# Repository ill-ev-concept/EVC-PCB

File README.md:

# EVC-PCB

*By: Himesh Nasaka*

Welcome to EV Concept's PCB Repo!

This is where all of our projects are stored. 

* Boards: Contains design files of all current boards being worked on
* Libs: Contains a wide selection of schematics, footprints, and models of components that are being used

# Getting Started

Start by having Git and KiCAD 10 downloaded. If you are using a older version of KiCAD, we recommend updating to the newest version. We also recommend installing Github Desktop in order to make the usage a bit cleaner.

Clone this repo. This can be either done through terminal or Github Desktop. Click the green dropdown labeled "<> Code" and select your preference of how to clone the repo. If using terminal, run the command below

```git clone [INSERT]```

If using Desktop, you can click the dropdown menu next to current repository, then "add", and finally "clone" where we can input the repo's url. 

# Setting Paths

After cloning, open KiCAD and find the "Preferences" dropdown and select "Configure Paths".
We are going to be adding three new paths. Create three new variables, ```EVC_SYMBOL_DIR```, ```EVC_FOOTPRINT_DIR```, and ```EVC_3DMODEL_DIR```. Link these to the location of the ```symbols```, ```footprints```, and ```3d_models``` folders contained with ```libs``` folder.

When designing, we will need KiCAD to know to look at a given library. We can do this by going to "Preferences" and finding either "Manage Symbol Libraries" or "Manage Footprint Libraries". Opening either brings up a window where we can select "Project Specific Libraries" where we can add paths. Click the folder icon and add the wanted library. If you set the path up correctly, the library path will contain  ```${EVC_SYMBOL_DIR}```, ```${EVC_FOOTPRINT_DIR}```, or ```${EVC_3DMODEL_DIR}```. 

# Contributing 

In order to begin designing, create a branch for your given board. This can be done through either the "current branch" dropdown in Desktop or using the command ```git checkout -b [branch name]```. You can swap branches using the same dropdown or either ```git checkout [branch name]```. 

This will be the branch where you will be doing your design work. Create a new KiCAD project and save the location into the boards folder of this repo. Everything onward will be traditional git. Use ```git add``` or check off the needed boxes on Desktop to add files for commit. ```git commit -m "[MESSAGE HERE]"``` will commit your changes. Make sure to write a meaningful commit message in order for good documentation. An example is shown below.

```git commit -m "Finished designing LDO and CANBus connectors, need to add MCU pinout and decoupling caps"```

Input both your contributions and the next required steps in order to give reminders to both yourself and your teammates. 

Once a board is finished or you want it reviewed, it must be submitted via a pull request. This can be done using ```git push -u origin [branch name]``` or by clicking the branch dropdown in Desktop and selecting the "create pull request" option.

This will open up a Github tab on your browser where you can edit your pull request. Give it a good title and description so the design choices are clear and understandable. A title will also help the leads parse what you guys want done. 

You'll see the image above if you use a command line prompt and go to the repo.

After the PR is submitted, we will decide on whether the board can be pushed to main or not. If it is not pushed, we will submit comments on what needs to be reviewed and edited. You can view open PRs and their comments in Github.

Apart from designing in KiCAD, it is important to be updating the libs folder when any new schematic, footprint, or model is added. First make sure the IC you want to add isn't currently within our library. Add the path to the specific library which is detailed more above. If the IC is not located in it's library, open Symbol/Footprint editor and select the library you want to add to. I recommended clicking the "View" dropdown, selecting the "Panels" option and adding the "Library Tree" option in order to easily see the connected libraries. 

From this, import the downloaded model and save the file. From there, push the updated library files and create a pull request. The leads will then check your work and merge it into main so everyone can use the IC.

When making pull requests for ICs, make sure to push them individually rather than with changes to other files. This will make it more clear for reviewers to understand that library files are being edited in addition to making sure that the change will be pushed to main. If you push with changes to your board and the pull request is not granted, people will not have access to the IC you have imported. 

Because the libs folder will be constantly updated, its also important to keep your branch up to date with new changes. We can layer on changes from main into our branch using a few different methods but the main one we will be using is merge. Run the command ```git fetch origin``` and then ```git merge origin``` in order to update changes. In Desktop, you can select "Update from main" from the "Branch" dropdown. 

This should not change any local files that is stored and will update the libs folder to have the newest selection of ICs. I recommend doing this every time you work on your boards. It will also make sure a merge conflict won't be created, in which the same file from two different pull requests is edited, causing a lot of hassle for the writers of this repo. 

A general outline of what the workflow may look like is shown below:

```git checkout [branch name]``` -> Run this to swap to the branch you want to work on

```git fetch origin``` -> Run this to pull updates from main. Important for having updated libs

```git merge origin/main``` -> Merges the changes from the above command

```git add [file name]``` -> Add files for commit. When updating library files, make sure to add them in individual PRs

```git commit -m "[message here]"``` -> Commits your changes to be pushed into your branch

```git push -u origin [branch name]``` -> Run this command the first time you make the branch. It will link your branch to Github. 

```git push``` -> Pushes your changes. After, you can go to Github and create a pull request for the changes to be pushed into main. **Don't create a PR for every change you do.** Only create pull requests **IF** you are editing the libs folder **OR** you are submitting for board revision **OR** it is the final revision of the board.

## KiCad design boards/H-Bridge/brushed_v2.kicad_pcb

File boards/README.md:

# Boards!

This is the location where you will be pushing your KiCAD files to. 
Each file should be it's own project. You should only be pushing 5 different files
- kicad_pro
- kicad_sch
- kicad_pcb
- fp-lib-table
- sym-lib-table

*Nothing else should be pushed*

I'll be adding more details later on

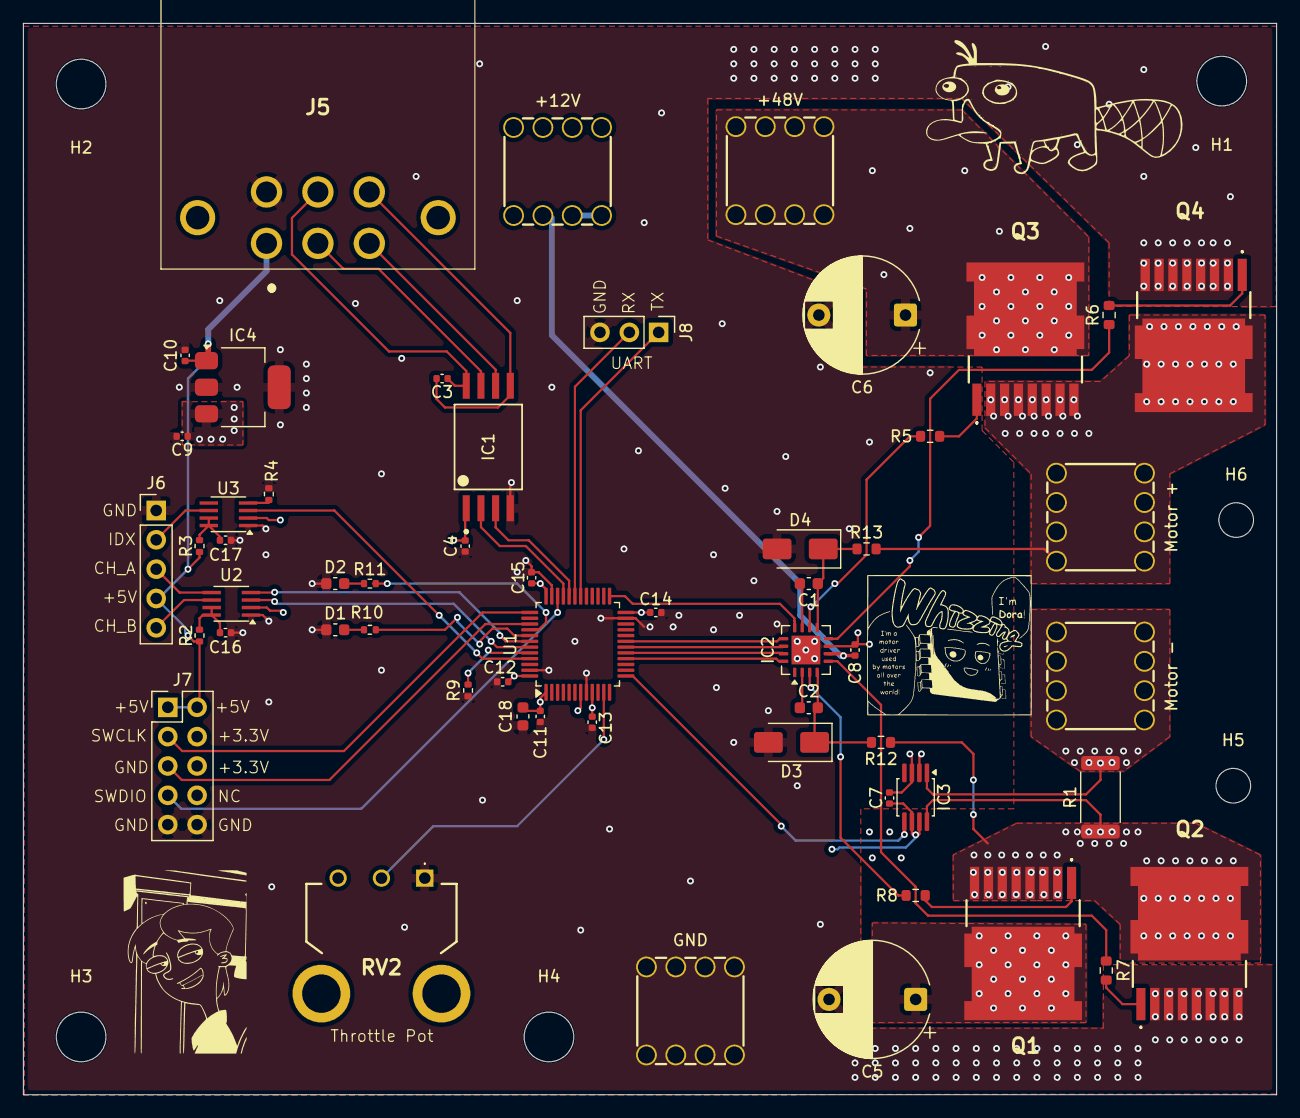
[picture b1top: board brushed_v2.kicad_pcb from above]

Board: 4 copper layers, 108.5 x 92.8 mm, 62 parts (0 on the bottom side), 52 nets.

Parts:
+12V: 12V+; WP-BUTR_7460307
+48V: V+; WP-BUTR_7460307
C1: 1uf; C_0603_1608Metric
C2: 1uF; C_0603_1608Metric
C3, C4, C7, C8, C11, C12, C13, C14, C15, C16, C17: 0.1uF; C_0402_1005Metric
C5, C6: 470uF; CP_Radial_D10.0mm_P7.50mm
C9, C10: 1uF; C_0402_1005Metric
C18: 4.7uF; C_0603_1608Metric
D1, D2: LED; C_0603_1608Metric
D3, D4: SS1200; D_SMA
GND: V-; WP-BUTR_7460307
H1, H2, H3, H4: MountingHole; MountingHole_4.3mm_M4
H5, H6: MountingHole; MountingHole_3mm
IC1: ISO1042QDWVQ1; DWV0008A-IPC_A
IC2: MIC4606-1YML-TR; QFN-16-1EP_4x4mm_P0.65mm_EP2.5x2.5mm
IC3: AD8410AWBRZ-RL; MSOP-8_3x3mm_P0.65mm
IC4: TC1108-3.3VDBTR; SOT-223
J5: DTF13-6P; DTF136P
J6: Encoder; PinHeader_1x05_P2.54mm_Vertical
J7: Prog_Header; PinHeader_2x05_P2.54mm_Vertical
J8: UART; PinHeader_1x03_P2.54mm_Vertical
Motor +: Motor-; WP-BUTR_7460307
Motor -: Motor+; WP-BUTR_7460307
Q1, Q2, Q3, Q4: NTBLS4D0N15MC
R1: .001; R_2512_6332Metric
R2, R3: 200k; R_0402_1005Metric
R4, R9: 10k; R_0402_1005Metric
R5, R6, R7, R8: 10; R_0603_1608Metric
R10, R11: 330; R_0402_1005Metric
R12, R13: 3; R_0603_1608Metric
RV2: Debug Throttle; P120PKY25BR10K
U1: STM32F103C8Tx; LQFP-48_7x7mm_P0.5mm
U2, U3: LSF0102DCUR; SSOP-8_2.95x2.8mm_P0.65mm

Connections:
+3.3V: C4.1, C7.1, C9.1, C11.1, C12.1, C13.1, C14.1, C15.1, C18.1, IC1.1 (VCC1), IC3.6 (VS), IC3.7 (VREF1), IC4.3 (VOUT), J7.4, J7.6, RV2.3, U1.1 (VBAT), U1.7 (NRST), U1.9 (VDDA), U1.24 (VDD), U1.36 (VDD), U1.48 (VDD), U2.2 (VREF_A), U3.2 (VREF_A)
+5V: C10.1, IC4.1 (VIN), J5.1, J6.4, J7.1, J7.2, R2.1, R3.1
+12V: +12V.1 (Pin_1_1), C8.1, IC2.6 (VDD)
+48V: +48V.1 (Pin_1_1), C5.1, C6.1, Q1.9 (D_1), Q1.10 (D_2), Q1.11 (D_3), Q1.12 (D_4), Q1.13 (D_5), Q3.9 (D_1), Q3.10 (D_2), Q3.11 (D_3), Q3.12 (D_4), Q3.13 (D_5)
/High Voltage&Sense/AHS: C2.2, D3.1 (K), IC2.4 (AHS), R12.2
/High Voltage&Sense/BHS: C1.1, D4.1 (K), IC2.9 (BHS), R13.1
/High Voltage&Sense/GATEA_HIGH: Q1.8 (G), R8.2
/High Voltage&Sense/GATEA_LOW: Q2.8 (G), R7.1
/High Voltage&Sense/GATEB_HIGH: Q3.8 (G), R5.2
/High Voltage&Sense/GATEB_LOW: Q4.8 (G), R6.2
/High Voltage&Sense/SHUNT+: IC3.8 (+IN), Q1.1 (S_1), Q1.2 (S_2), Q1.3 (S_3), Q1.4 (S_4), Q1.5 (S_5), Q1.6 (S_6), Q1.7 (S_7), Q2.9 (D_1), Q2.10 (D_2), Q2.11 (D_3), Q2.12 (D_4), Q2.13 (D_5), R1.1, R12.1
/High Voltage&Sense/SHUNT-: IC3.1 (-IN), Motor -.1 (Pin_1_1), R1.2
/MCU&Low_Voltage/AHI: IC2.16 (AHI), U1.16 (PA6)
/MCU&Low_Voltage/ALI: IC2.15 (ALI), U1.17 (PA7)
/MCU&Low_Voltage/BHI: IC2.13 (BHI), U1.19 (PB1)
/MCU&Low_Voltage/BLI: IC2.14 (BLI), U1.18 (PB0)
/MCU&Low_Voltage/CAN5V: C3.1, IC1.8 (VCC2), J5.5
/MCU&Low_Voltage/CANGND: C3.2, IC1.5 (GND2), J5.4
/MCU&Low_Voltage/CANH: IC1.7 (CANH), J5.2
/MCU&Low_Voltage/CANL: IC1.6 (CANL), J5.3
/MCU&Low_Voltage/CAN_RX: IC1.3 (RXD), U1.32 (PA11)
/MCU&Low_Voltage/CAN_TX: IC1.2 (TXD), U1.33 (PA12)
/MCU&Low_Voltage/CHA_3.3: U1.42 (PB6), U2.4 (A2)
/MCU&Low_Voltage/CHB_3.3: U1.43 (PB7), U2.3 (A1)
/MCU&Low_Voltage/CH_A: J6.3, U2.5 (B2)
/MCU&Low_Voltage/CH_B: J6.5, U2.6 (B1)
/MCU&Low_Voltage/GATE_EN: IC2.12 (EN), U1.25 (PB12)
/MCU&Low_Voltage/IDX: J6.2, U3.6 (B1)
/MCU&Low_Voltage/IDX_3.3: U1.45 (PB8), U3.3 (A1)
/MCU&Low_Voltage/LED_1: R10.1, U1.41 (PB5)
/MCU&Low_Voltage/LED_2: R11.1, U1.40 (PB4)
/MCU&Low_Voltage/POT_IN: RV2.2, U1.11 (PA1)
/MCU&Low_Voltage/SENSE: IC3.5 (OUT), U1.13 (PA3)
/MCU&Low_Voltage/SWCLK: J7.3, U1.37 (PA14)
/MCU&Low_Voltage/SWDIO: J7.7, U1.34 (PA13)
/MCU&Low_Voltage/SWO: J7.5, U1.39 (PB3)
/MCU&Low_Voltage/UART_RX: J8.2, U1.31 (PA10)
/MCU&Low_Voltage/UART_TX: J8.1, U1.30 (PA9)
GND: C4.2, C5.2, C6.2, C7.2, C8.2, C9.2, C10.2, C11.2, C12.2, C13.2, C14.2, C15.2, C16.2, C17.2, C18.2, D1.1 (K), D2.1 (K), D3.2 (A), D4.2 (A), GND.1 (Pin_1_1), IC1.4 (GND1), IC2.7 (VSS), IC2.17 (GND), IC3.2 (GND), IC3.3 (VREF2), IC4.2 (GND_1), IC4.4 (GND_2), J5.6, J6.1, J7.9, J7.10, J8.3, Q2.1 (S_1), Q2.2 (S_2), Q2.3 (S_3), Q2.4 (S_4), Q2.5 (S_5), Q2.6 (S_6), Q2.7 (S_7), Q4.1 (S_1), Q4.2 (S_2), Q4.3 (S_3), Q4.4 (S_4), Q4.5 (S_5), Q4.6 (S_6), Q4.7 (S_7), R4.1, R9.2, RV2.1, U1.8 (VSSA), U1.23 (VSS), U1.35 (VSS), U1.47 (VSS), U2.1 (GND), U3.1 (GND)
unnamed: D1.2 (A), R10.2
unnamed: D2.2 (A), R11.2
unnamed: C2.1, IC2.2 (AHB)
unnamed: IC2.3 (AHO), R8.1
unnamed: IC2.5 (ALO), R7.2
unnamed: C1.2, IC2.11 (BHB)
unnamed: IC2.10 (BHO), R5.1
unnamed: IC2.8 (BLO), R6.1
unnamed: Motor +.1 (Pin_1_1), Q3.1 (S_1), Q3.2 (S_2), Q3.3 (S_3), Q3.4 (S_4), Q3.5 (S_5), Q3.6 (S_6), Q3.7 (S_7), Q4.9 (D_1), Q4.10 (D_2), Q4.11 (D_3), Q4.12 (D_4), Q4.13 (D_5), R13.2
unnamed: R9.1, U1.44 (BOOT0)
unnamed: C16.1, R2.2, U2.7 (VREF_B), U2.8 (EN)
unnamed: R4.2, U3.4 (A2)
unnamed: C17.1, R3.2, U3.7 (VREF_B), U3.8 (EN)

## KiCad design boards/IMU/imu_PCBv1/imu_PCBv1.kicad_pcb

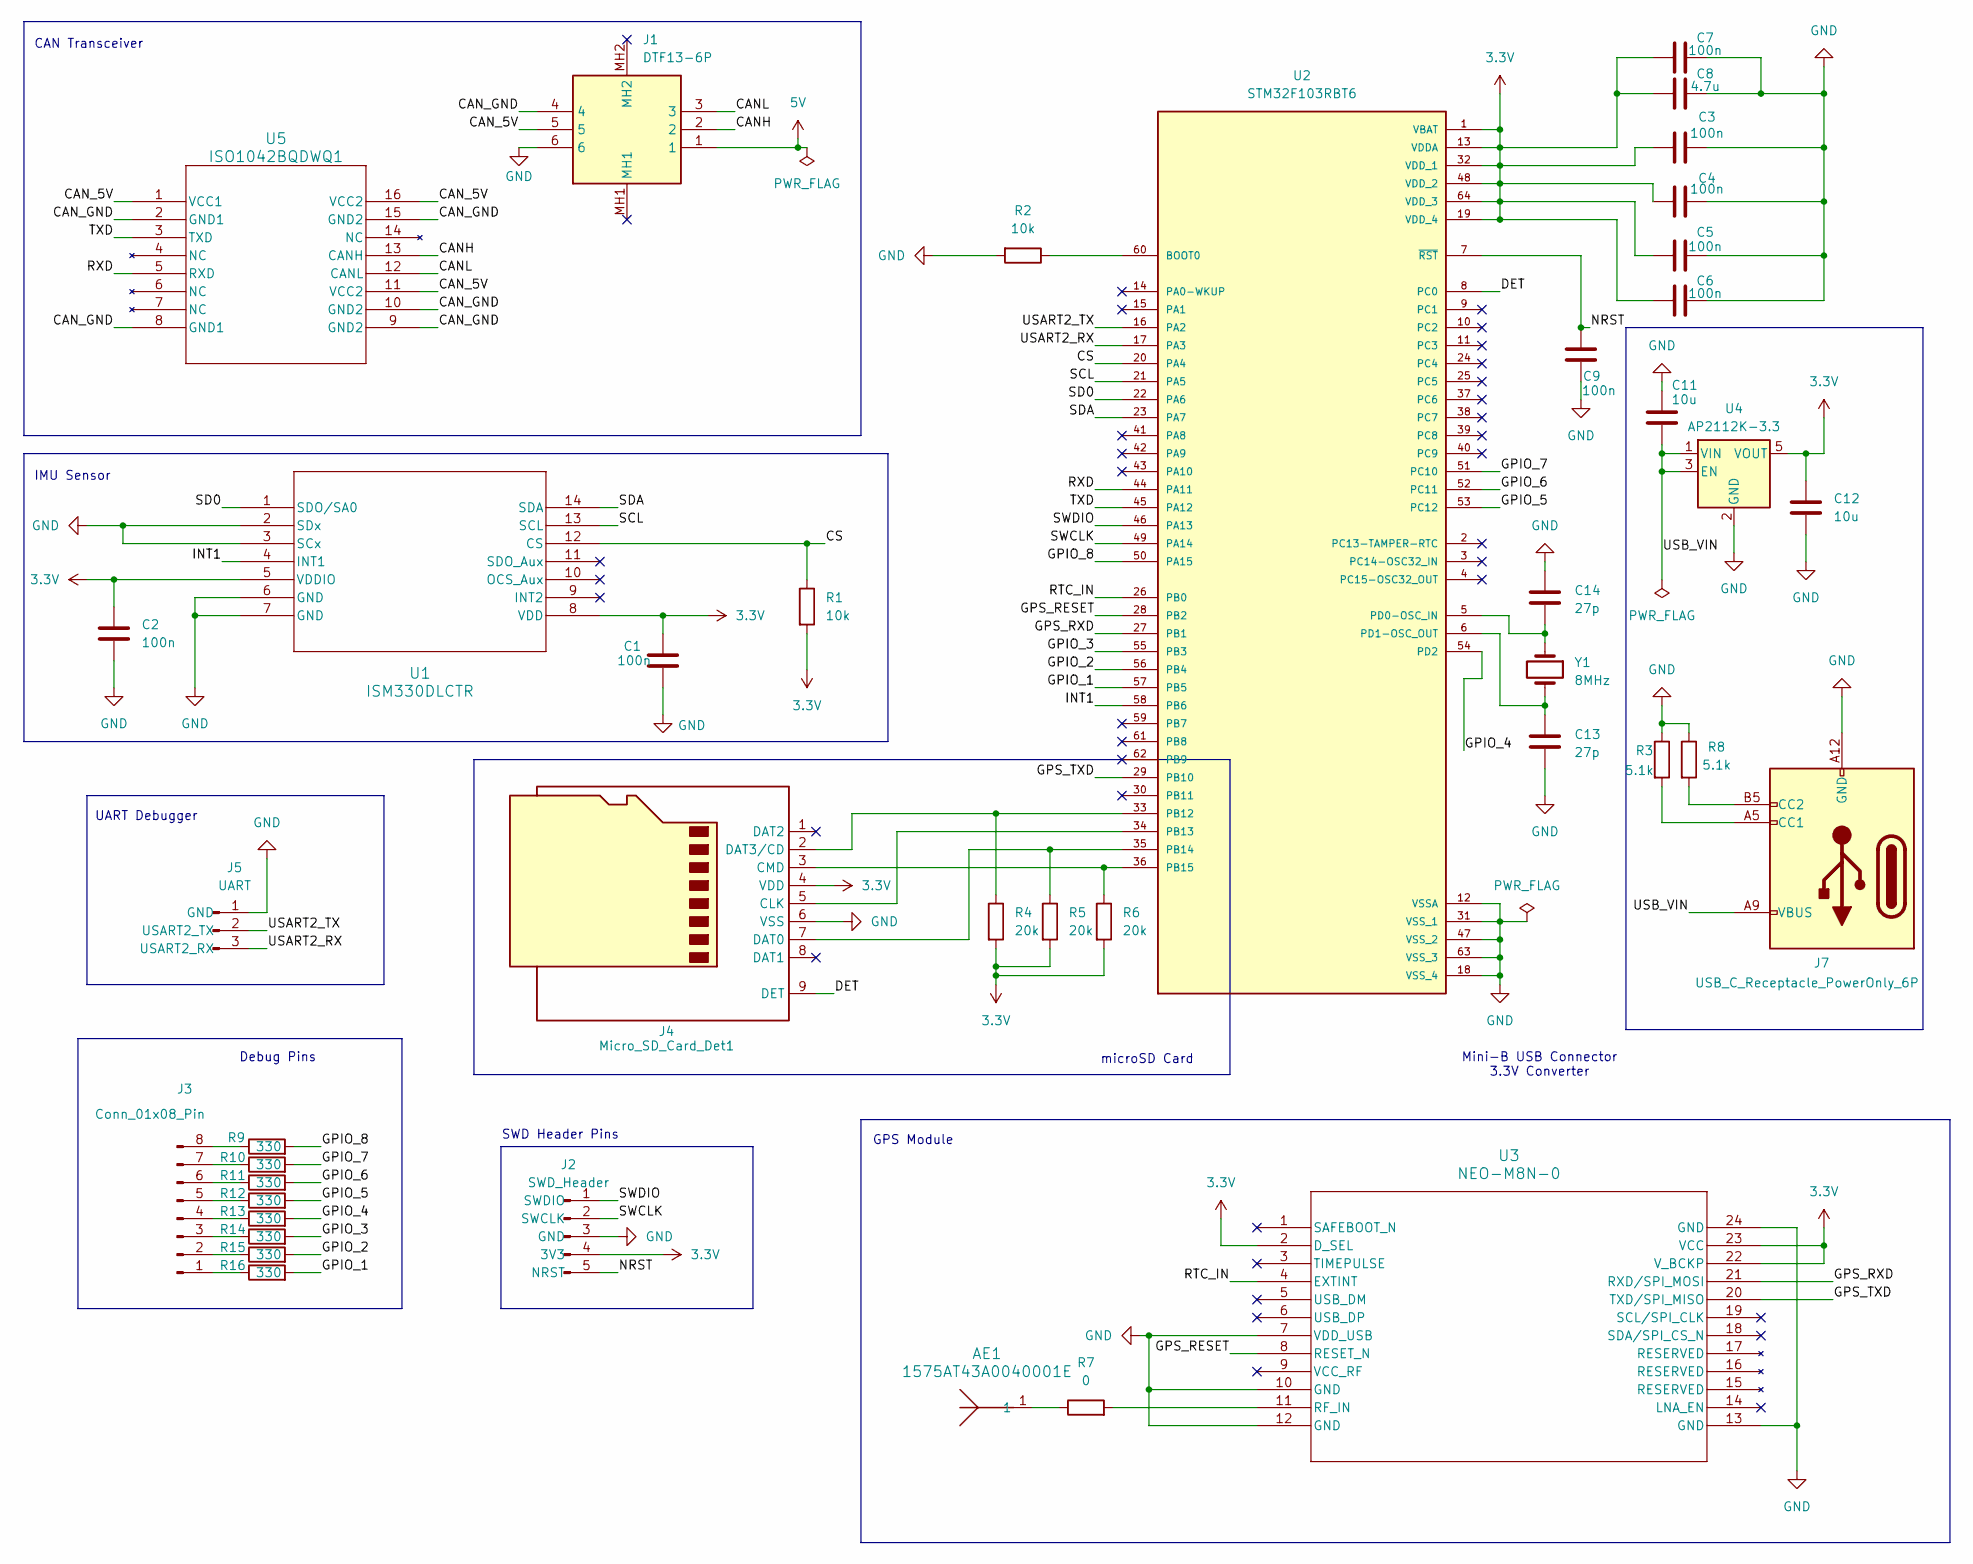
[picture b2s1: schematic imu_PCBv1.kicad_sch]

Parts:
AE1: 1575AT43A0040001E; antenna
C1, C2, C3, C4, C5, C6, C7, C9: 100n; C_0603_1608Metric_Pad1.08x0.95mm_HandSolder
C8: 4.7u; C_0603_1608Metric_Pad1.08x0.95mm_HandSolder
C11, C12: 10u; C_0603_1608Metric_Pad1.08x0.95mm_HandSolder
C13, C14: 27p; C_0603_1608Metric_Pad1.08x0.95mm_HandSolder
J1: DTF13-6P; EVC_CANconnector; Manufacturer_Part_Number DTF13-6P; Mouser Part Number 571-DTF13-6P
J2: SWD_Header; PinHeader_1x05_P2.54mm_Vertical
J3: Conn_01x08_Pin; PinHeader_1x08_P2.54mm_Vertical
J4: Micro_SD_Card_Det1; microSD_CardConnector_MSD-4-A
J5: UART; FanPinHeader_1x03_P2.54mm_Vertical
J7: USB_C_Receptacle_PowerOnly_6P; USB_Connector
R1, R2: 10k; R_0603_1608Metric_Pad0.98x0.95mm_HandSolder
R3, R8: 5.1k; R_0603_1608Metric_Pad0.98x0.95mm_HandSolder
R4, R5, R6: 20k; R_0603_1608Metric_Pad0.98x0.95mm_HandSolder
R7: 0; R_0603_1608Metric_Pad0.98x0.95mm_HandSolder
R9, R10, R11, R12, R13, R14, R15, R16: 330; R_0603_1608Metric_Pad0.98x0.95mm_HandSolder
U1: ISM330DLCTR; ISM330DLCTR-M
U2: STM32F103RBT6; STM32F103RBT6-10x10mm; PARTREV 20; DigiKey_Part_Number 497-6066-ND
U3: NEO-M8N-0; SNAP_NEO-M8N
U4: AP2112K-3.3; LinearRegulator_DIO-M
U5: ISO1042BQDWQ1; CAN-M
Y1: 8MHz; SOT-323_SC-70

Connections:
3.3V: C1.2, C2.2, C3.2, C4.2, C5.2, C6.2, C7.2, C8.2, C12.1, J2.4 (3V3), J4.4 (VDD), R1.2, R4.2, R5.2, R6.2, U1.5 (VDDIO), U1.8 (VDD), U2.1 (VBAT), U2.13 (VDDA), U2.19 (VDD_4), U2.32 (VDD_1), U2.48 (VDD_2), U2.64 (VDD_3), U3.2 (D_SEL), U3.22 (V_BCKP), U3.23 (VCC), U4.5 (VOUT)
5V: J1.1
/CANH: J1.2, U5.13 (CANH)
/CANL: J1.3, U5.12 (CANL)
/CAN_5V: J1.5, U5.1 (VCC1), U5.11 (VCC2), U5.16 (VCC2)
/CAN_GND: J1.4, U5.2 (GND1), U5.8 (GND1), U5.9 (GND2), U5.10 (GND2), U5.15 (GND2)
/CS: R1.1, U1.12 (CS), U2.20 (PA4)
/DET: J4.9 (DET), U2.8 (PC0)
/GPIO_1: R16.2, U2.57 (PB5)
/GPIO_2: R15.2, U2.56 (PB4)
/GPIO_3: R14.2, U2.55 (PB3)
/GPIO_4: R13.2, U2.54 (PD2)
/GPIO_5: R12.2, U2.53 (PC12)
/GPIO_6: R11.2, U2.52 (PC11)
/GPIO_7: R10.2, U2.51 (PC10)
/GPIO_8: R9.2, U2.50 (PA15)
/GPS_RESET: U2.28 (PB2), U3.8 (RESET_N)
/GPS_RXD: U2.27 (PB1), U3.21 (RXD/SPI_MOSI)
/GPS_TXD: U2.29 (PB10), U3.20 (TXD/SPI_MISO)
/INT1: U1.4 (INT1), U2.58 (PB6)
/NRST: C9.2, J2.5 (NRST), U2.7 (~RST)
/RTC_IN: U2.26 (PB0), U3.4 (EXTINT)
/RXD: U2.44 (PA11), U5.5 (RXD)
/SCL: U1.13 (SCL), U2.21 (PA5)
/SD0: U1.1 (SDO/SA0), U2.22 (PA6)
/SDA: U1.14 (SDA), U2.23 (PA7)
/SWCLK: J2.2 (SWCLK), U2.49 (PA14)
/SWDIO: J2.1 (SWDIO), U2.46 (PA13)
/TXD: U2.45 (PA12), U5.3 (TXD)
/USART2_RX: J5.3 (USART2_RX), U2.17 (PA3)
/USART2_TX: J5.2 (USART2_TX), U2.16 (PA2)
/USB_VIN: C11.2, J7.A9 (VBUS), J7.B9 (VBUS), U4.1 (VIN), U4.3 (EN)
GND: C1.1, C2.1, C3.1, C4.1, C5.1, C6.1, C7.1, C8.1, C9.1, C11.1, C12.2, C13.2, C14.1, J1.6, J2.3 (GND), J4.6 (VSS), J5.1 (GND), J7.A12 (GND), J7.B12 (GND), R2.2, R3.1, R8.1, U1.2 (SDx), U1.3 (SCx), U1.6 (GND), U1.7 (GND), U2.12 (VSSA), U2.18 (VSS_4), U2.31 (VSS_1), U2.47 (VSS_2), U2.63 (VSS_3), U3.7 (VDD_USB), U3.10 (GND), U3.12 (GND), U3.13 (GND), U3.24 (GND), U4.2 (GND)
unnamed: AE1.1 (1_1), R7.1
unnamed: J3.1, R16.1
unnamed: J3.2, R15.1
unnamed: J3.3, R14.1
unnamed: J3.4, R13.1
unnamed: J3.5, R12.1
unnamed: J3.6, R11.1
unnamed: J3.7, R10.1
unnamed: J3.8, R9.1
unnamed: J4.5 (CLK), U2.34 (PB13)
unnamed: J4.3 (CMD), R6.1, U2.36 (PB15)
unnamed: J4.7 (DAT0), R5.1, U2.35 (PB14)
unnamed: J4.2 (DAT3/CD), R4.1, U2.33 (PB12)
unnamed: J7.A5 (CC1), R3.2
unnamed: J7.B5 (CC2), R8.2
unnamed: R2.1, U2.60 (BOOT0)
unnamed: C14.2, U2.5 (PD0-OSC_IN), Y1.1
unnamed: C13.1, U2.6 (PD1-OSC_OUT), Y1.2
unnamed: R7.2, U3.11 (RF_IN)

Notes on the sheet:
microSD Card
GPS Module
Mini-B USB Connector 3.3V Converter
UART Debugger
Debug Pins
SWD Header Pins
IMU Sensor
CAN Transceiver

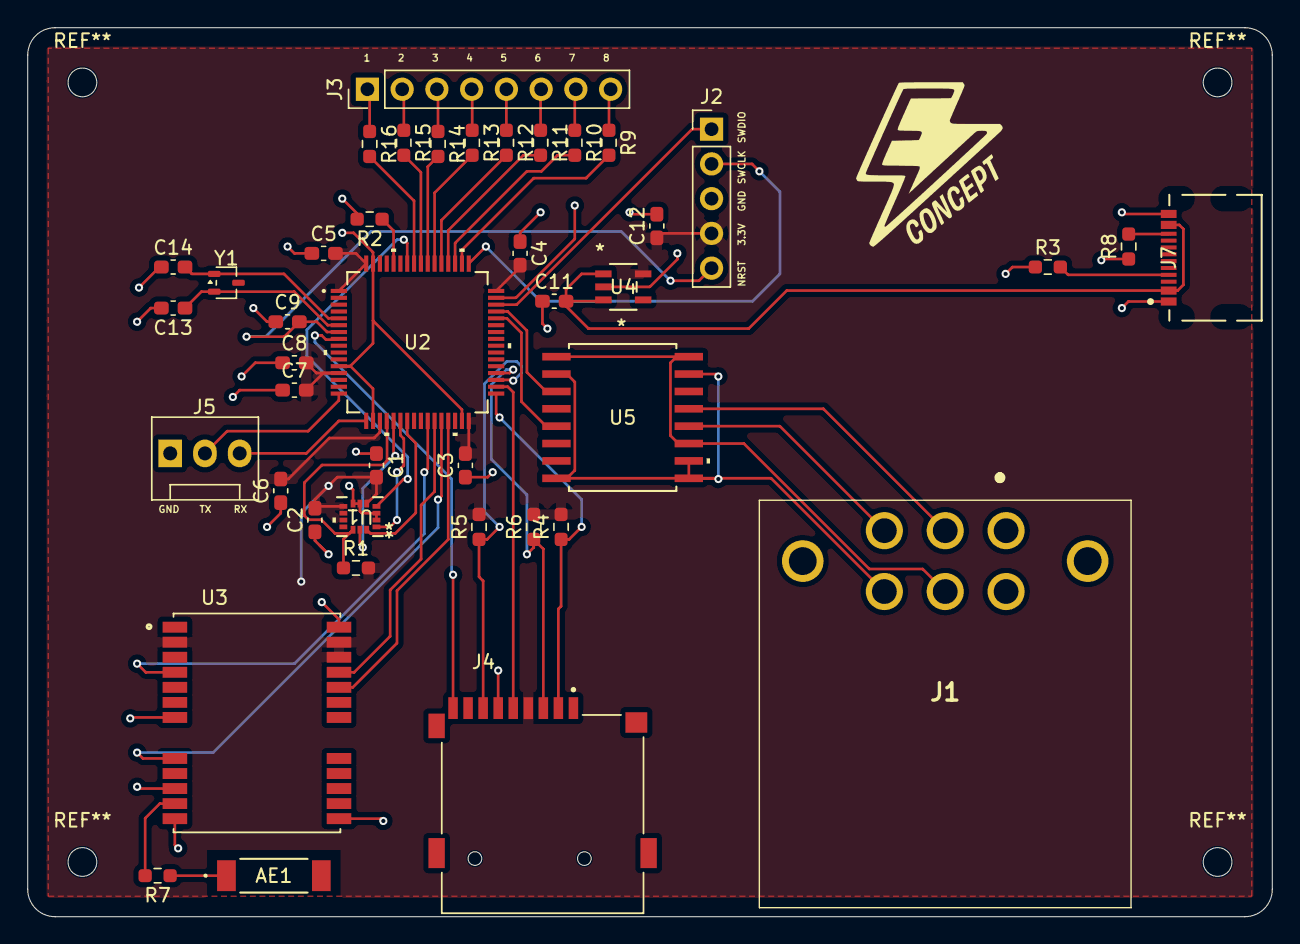
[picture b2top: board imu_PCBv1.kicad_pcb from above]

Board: 2 copper layers, 91.0 x 65.0 mm, 42 parts (0 on the bottom side), 51 nets.

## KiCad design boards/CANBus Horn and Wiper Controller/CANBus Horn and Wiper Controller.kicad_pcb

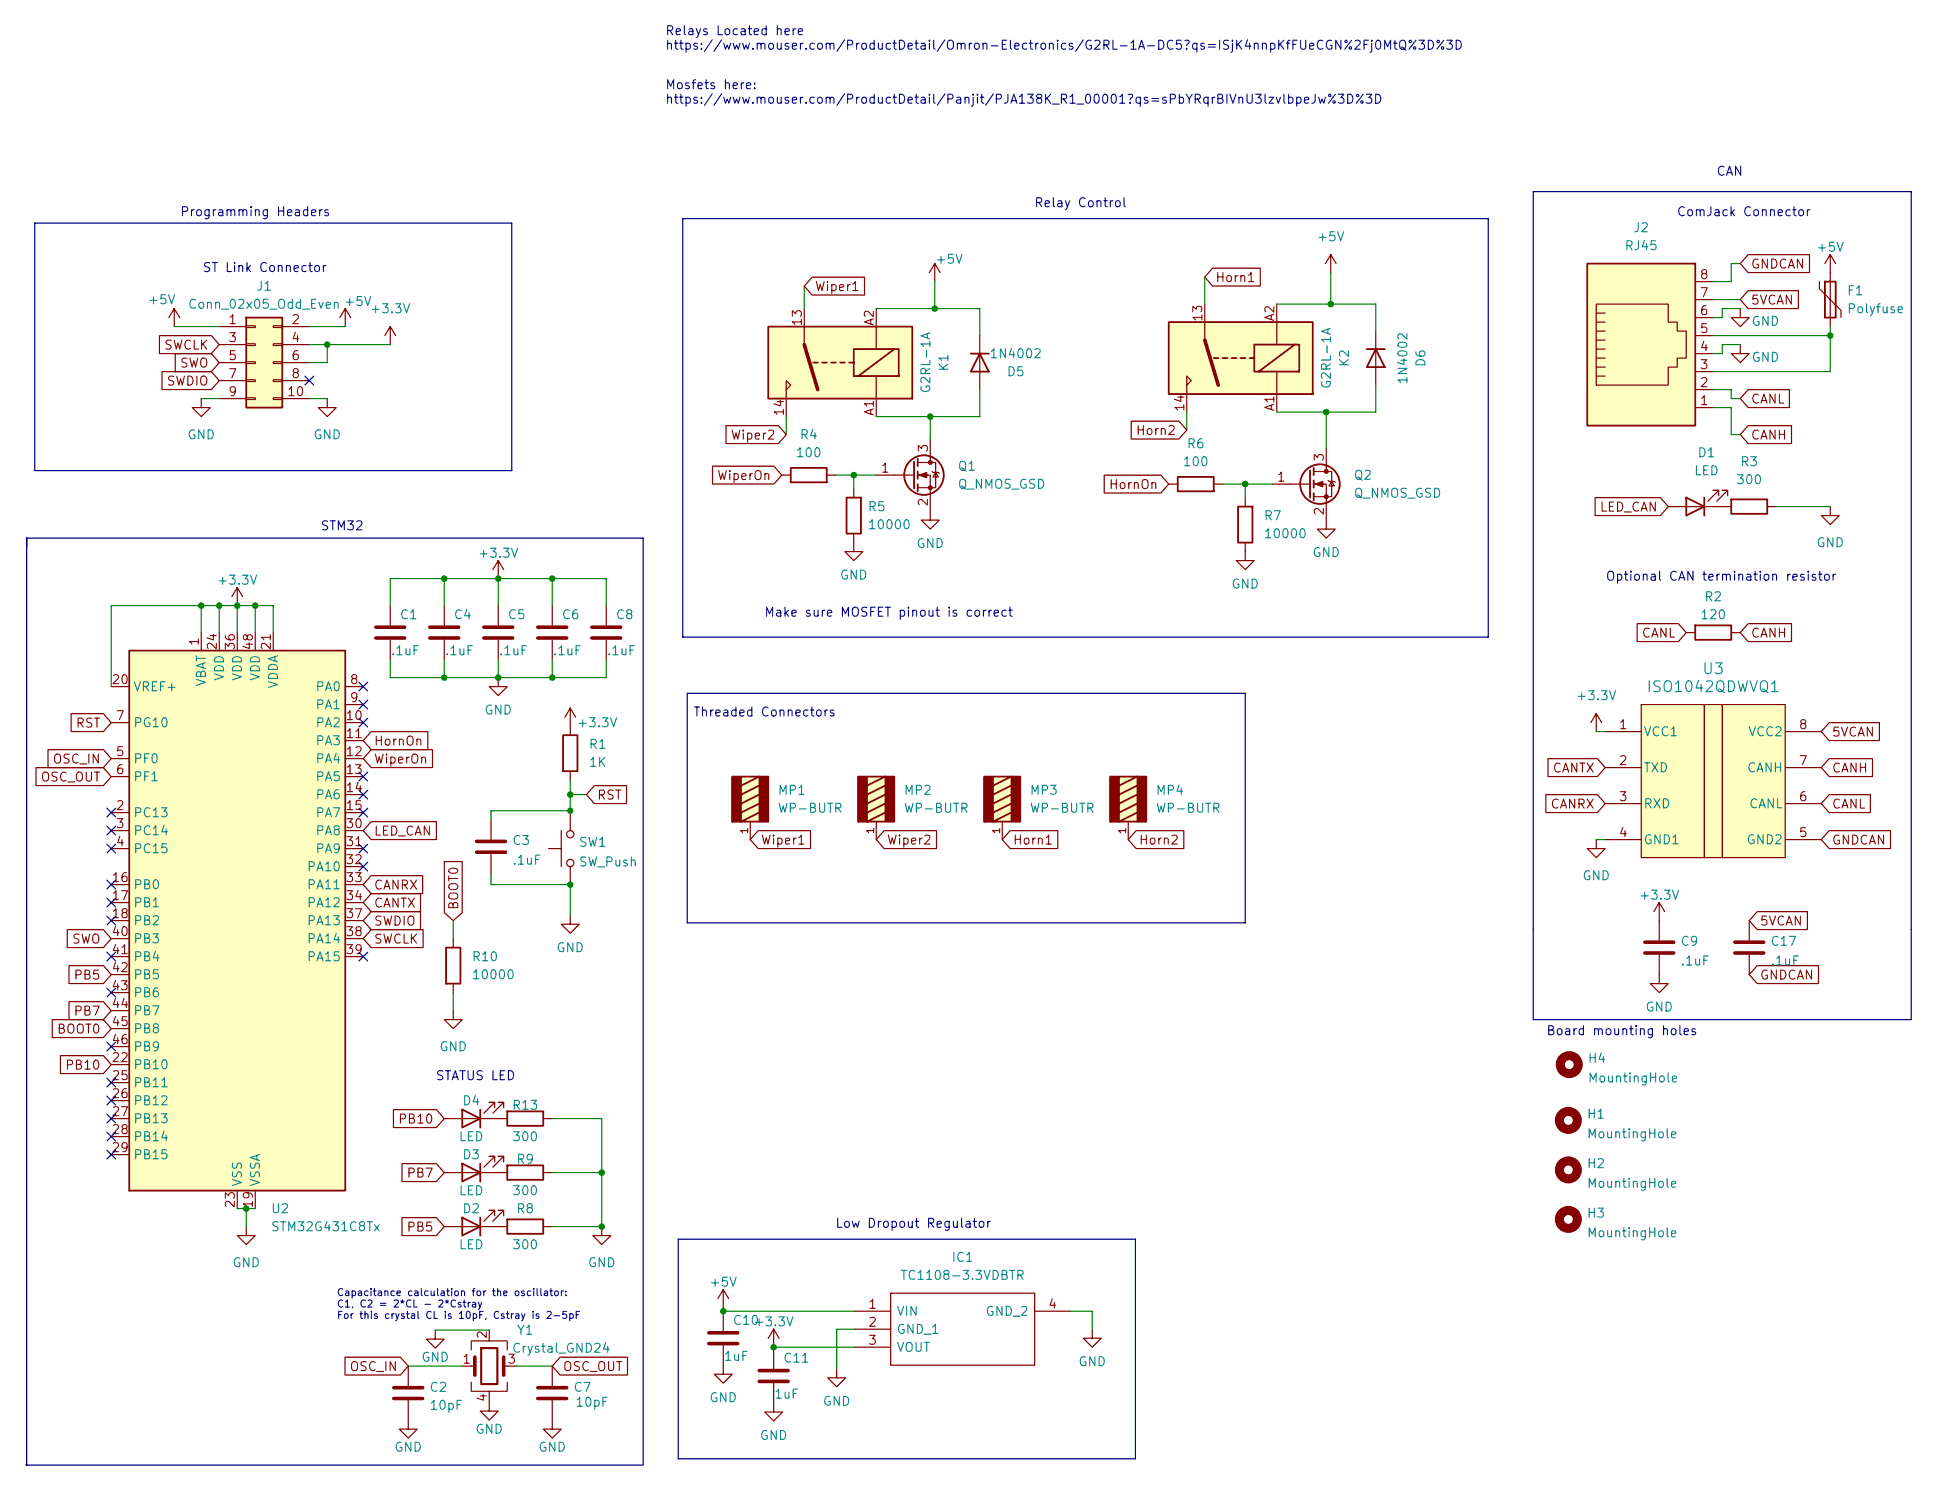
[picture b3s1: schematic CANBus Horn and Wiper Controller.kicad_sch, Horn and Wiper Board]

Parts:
C1, C3, C4, C5, C6, C8, C9, C17: .1uF; C_0805_2012Metric
C2, C7: 10pF; C_0603_1608Metric
C10, C11: 1uF; C_0805_2012Metric
D1, D2, D3, D4: LED; LED_0603_1608Metric
D5, D6: 1N4002; D_DO-41_SOD81_P10.16mm_Horizontal
F1: Polyfuse; Fuse_0805_2012Metric
H1, H2, H3, H4: MountingHole; MountingHole_3.2mm_M3
IC1: TC1108-3.3VDBTR; SOT230P700X180-4N; Mouser Part Number 579-TC1108-3.3VDBTR
J1: Conn_02x05_Odd_Even; PinSocket_2x05_P2.54mm_Vertical
J2: RJ45; RJ45_Amphenol_54602-x08_Horizontal
K1, K2: G2RL-1A; Relay_SPST_Omron_G2RL-1A
MP1, MP2, MP3, MP4: WP-BUTR; WP-BUTR_7460307; DigiKey_Part_Number 732-3201-ND
Q1, Q2: Q_NMOS_GSD; SOT-23-3
R1: 1K; R_0805_2012Metric
R2: 120; R_0805_2012Metric
R3, R8, R9, R13: 300; R_0805_2012Metric
R4, R6: 100; R_0805_2012Metric
R5, R7: 10000; R_0805_2012Metric
R10: 10000; R_0508_1220Metric
SW1: SW_Push; SW_Push_SPST_NO_Alps_SKRK
U2: STM32G431C8Tx; LQFP-48_7x7mm_P0.5mm
U3: ISO1042QDWVQ1; SOIC8_ISO1042-Q1
Y1: Crystal_GND24; Crystal_SMD_3225-4Pin_3.2x2.5mm

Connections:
5VCAN: C17.1, J2.7, U3.8 (VCC2)
+3.3V: C1.1, C4.1, C5.1, C6.1, C8.1, C9.1, C11.1, IC1.3 (VOUT), J1.4, J1.6, R1.1, U2.1 (VBAT), U2.20 (VREF+), U2.21 (VDDA), U2.24 (VDD), U2.36 (VDD), U2.48 (VDD), U3.1 (VCC1)
+5V: C10.1, D5.1 (K), D6.1 (K), F1.1, IC1.1 (VIN), J1.1, J1.2, K1.A2, K2.A2
BOOT0: R10.1, U2.45 (PB8)
CANH: J2.1, R2.1, U3.7 (CANH)
CANL: J2.2, R2.2, U3.6 (CANL)
CANRX: U2.33 (PA11), U3.3 (RXD)
CANTX: U2.34 (PA12), U3.2 (TXD)
GND: C1.2, C2.2, C3.2, C4.2, C5.2, C6.2, C7.2, C8.2, C9.2, C10.2, C11.2, IC1.2 (GND_1), IC1.4 (GND_2), J1.9, J1.10, J2.4, J2.6, Q1.2 (S), Q2.2 (S), R3.1, R5.1, R7.1, R8.1, R9.1, R10.2, R13.1, SW1.1, U2.19 (VSSA), U2.23 (VSS), U2.35 (VSS), U2.47 (VSS), U3.4 (GND1), Y1.2, Y1.4
GNDCAN: C17.2, J2.8, U3.5 (GND2)
Horn1: K2.13, MP3.1, MP3.2, MP3.3, MP3.4, MP3.5, MP3.6, MP3.7, MP3.8
Horn2: K2.14, MP4.1, MP4.2, MP4.3, MP4.4, MP4.5, MP4.6, MP4.7, MP4.8
HornOn: R6.1, U2.11 (PA3)
LED_CAN: D1.2 (A), U2.30 (PA8)
unnamed: D1.1 (K), R3.2
unnamed: D2.1 (K), R8.2
unnamed: D3.1 (K), R9.2
unnamed: D4.1 (K), R13.2
unnamed: D5.2 (A), K1.A1, Q1.3 (D)
unnamed: D6.2 (A), K2.A1, Q2.3 (D)
unnamed: F1.2, J2.3, J2.5
unnamed: Q1.1 (G), R4.2, R5.2
unnamed: Q2.1 (G), R6.2, R7.2
OSC_IN: C2.1, U2.5 (PF0), Y1.1
OSC_OUT: C7.1, U2.6 (PF1), Y1.3
PB5: D2.2 (A), U2.42 (PB5)
PB7: D3.2 (A), U2.44 (PB7)
PB10: D4.2 (A), U2.22 (PB10)
RST: C3.1, R1.2, SW1.2, U2.7 (PG10)
SWCLK: J1.3, U2.38 (PA14)
SWDIO: J1.7, U2.37 (PA13)
SWO: J1.5, U2.40 (PB3)
Wiper1: K1.13, MP1.1, MP1.2, MP1.3, MP1.4, MP1.5, MP1.6, MP1.7, MP1.8
Wiper2: K1.14, MP2.1, MP2.2, MP2.3, MP2.4, MP2.5, MP2.6, MP2.7, MP2.8
WiperOn: R4.1, U2.12 (PA4)

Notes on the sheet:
Threaded Connectors
Optional CAN termination resistor
Relays Located here https://www.mouser.com/ProductDetail/Omron-Electronics/G2RL-1A-DC5?qs=ISjK4nnpKfFUeCGN%2Fj0MtQ%3D%3D
CAN
Mosfets here: https://www.mouser.com/ProductDetail/Panjit/PJA138K_R1_00001?qs=sPbYRqrBIVnU3lzvlbpeJw%3D%3D
Make sure MOSFET pinout is correct
ST Link Connector
Programming Headers
STM32
Capacitance calculation for the oscillator: C1, C2 = 2*CL - 2*Cstray For this crystal CL is 10pF, Cstray is 2-5pF
Low Dropout Regulator
STATUS LED
Board mounting holes
Relay Control
ComJack Connector

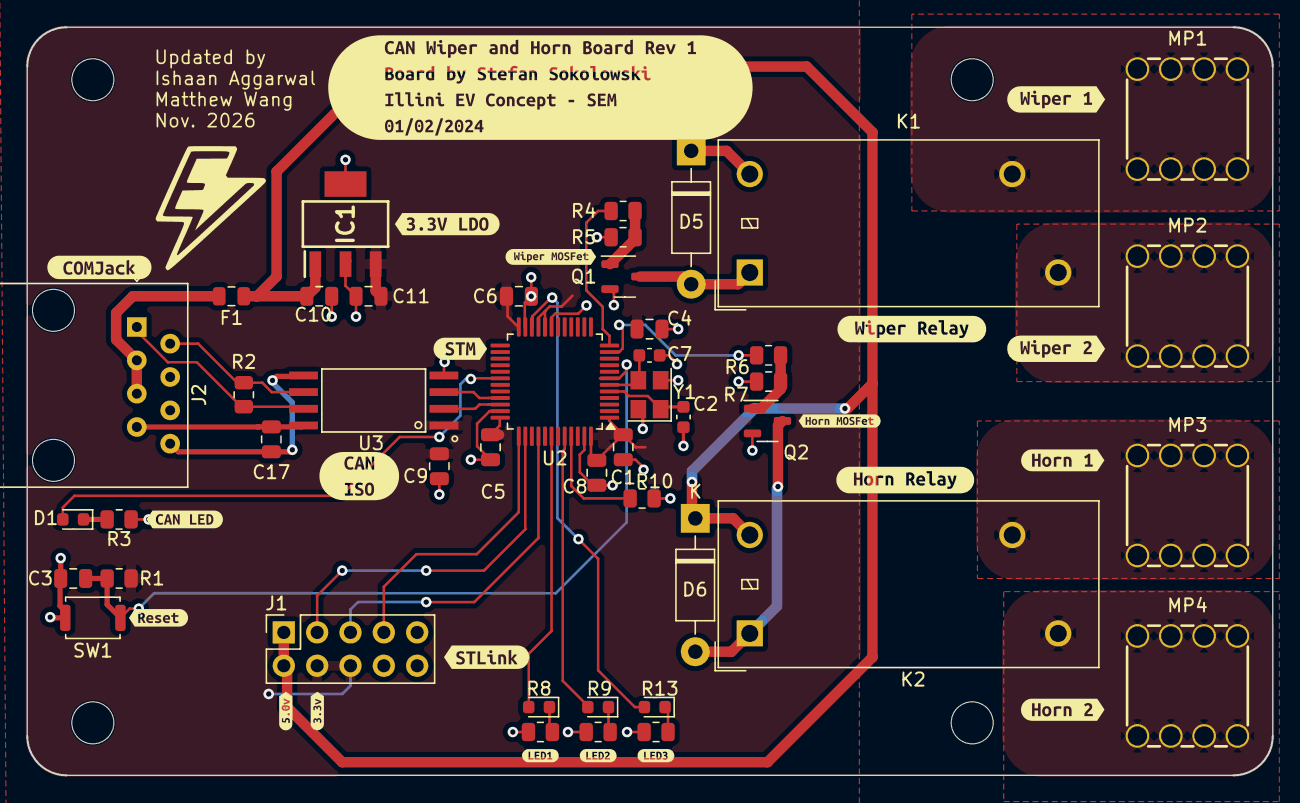
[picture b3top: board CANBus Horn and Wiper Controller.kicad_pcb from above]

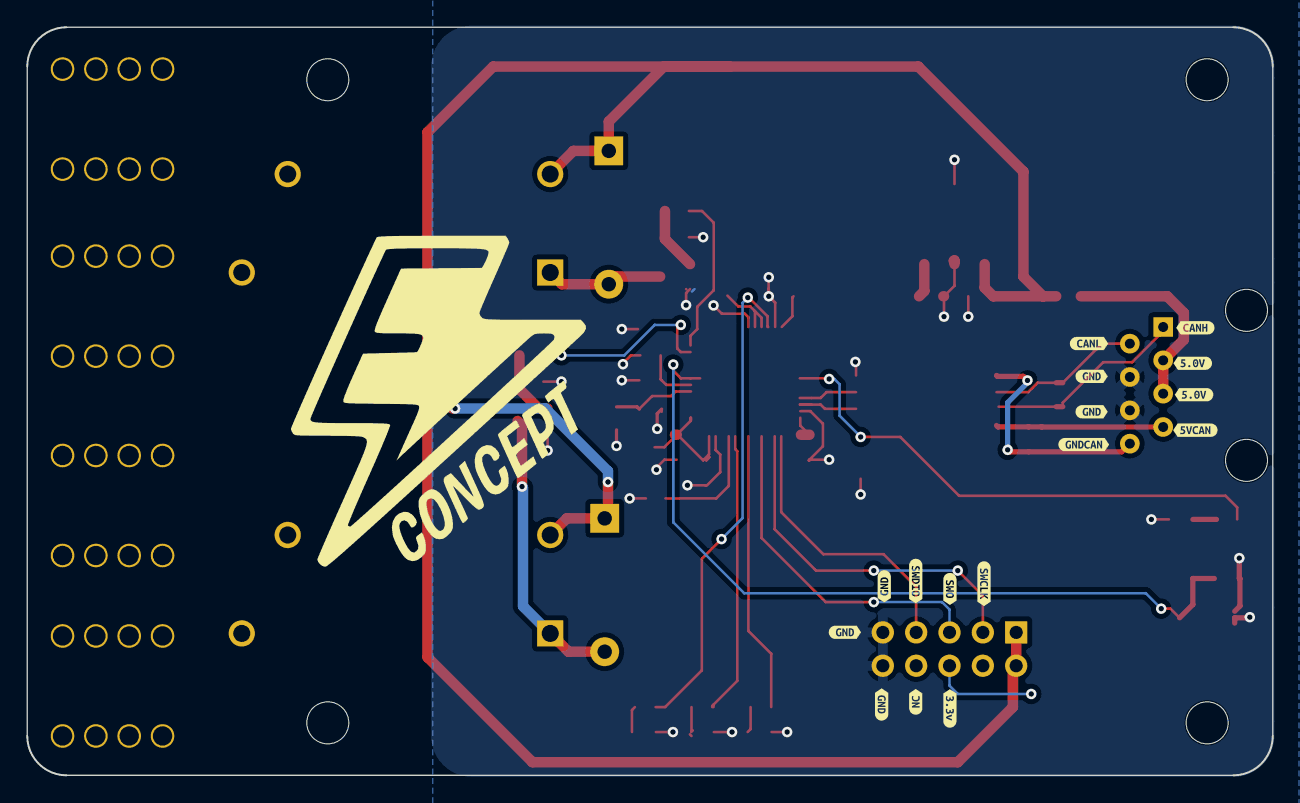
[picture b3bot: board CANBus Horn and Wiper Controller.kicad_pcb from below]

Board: 2 copper layers, 94.9 x 57.0 mm, 86 parts (16 on the bottom side), 35 nets.

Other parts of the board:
kibuzzard-6594C8CC: G***; kibuzzard-6594C8CC
kibuzzard-6594C8DC: G***; kibuzzard-6594C8DC
kibuzzard-6594C8F6: G***; kibuzzard-6594C8F6
kibuzzard-6594C90C: G***; kibuzzard-6594C90C
kibuzzard-6594C936: G***; kibuzzard-6594C936
kibuzzard-6594D000: G***; kibuzzard-6594D000
kibuzzard-6594D0D5: G***; kibuzzard-6594D0D5
kibuzzard-6594D0F7: G***; kibuzzard-6594D0F7
kibuzzard-6594D0FC: G***; kibuzzard-6594D0FC
kibuzzard-6594D0FF: G***; kibuzzard-6594D0FF
kibuzzard-6594D3A6: G***; kibuzzard-6594D3A6
kibuzzard-6594D3A9: G***; kibuzzard-6594D3A9
kibuzzard-6594D4D9: G***; kibuzzard-6594D4D9
kibuzzard-6594D4DE: G***; kibuzzard-6594D4DE
kibuzzard-6594D4E3: G***; kibuzzard-6594D4E3
kibuzzard-6594D4E9: G***; kibuzzard-6594D4E9
kibuzzard-6594D4F4: G***; kibuzzard-6594D4F4
kibuzzard-6594D4FA: G***; kibuzzard-6594D4FA
kibuzzard-6594D4FD: G***; kibuzzard-6594D4FD
kibuzzard-6594D12D: G***; kibuzzard-6594D12D
kibuzzard-6594D13F: G***; kibuzzard-6594D13F
kibuzzard-6594D22B: G***; kibuzzard-6594D22B
kibuzzard-6594D34E: G***; kibuzzard-6594D34E
kibuzzard-6594D39D: G***; kibuzzard-6594D39D
kibuzzard-6594D132: G***; kibuzzard-6594D132
kibuzzard-6594D138: G***; kibuzzard-6594D138
kibuzzard-6594D231: G***; kibuzzard-6594D231
kibuzzard-6594ECBA: G***; kibuzzard-6594ECBA
kibuzzard-6594ECC0: G***; kibuzzard-6594ECC0
kibuzzard-6594ECC9: G***; kibuzzard-6594ECC9
kibuzzard-6594ECCC: G***; kibuzzard-6594ECCC
kibuzzard-6594ED5E: G***; kibuzzard-6594ED5E
kibuzzard-6594ED81: G***; kibuzzard-6594ED81
kibuzzard-6594EE0A: G***; kibuzzard-6594EE0A
kibuzzard-6594EE20: G***; kibuzzard-6594EE20
kibuzzard-6594EF8F: G***; kibuzzard-6594EF8F
kibuzzard-6593999E: G***; kibuzzard-6593999E
